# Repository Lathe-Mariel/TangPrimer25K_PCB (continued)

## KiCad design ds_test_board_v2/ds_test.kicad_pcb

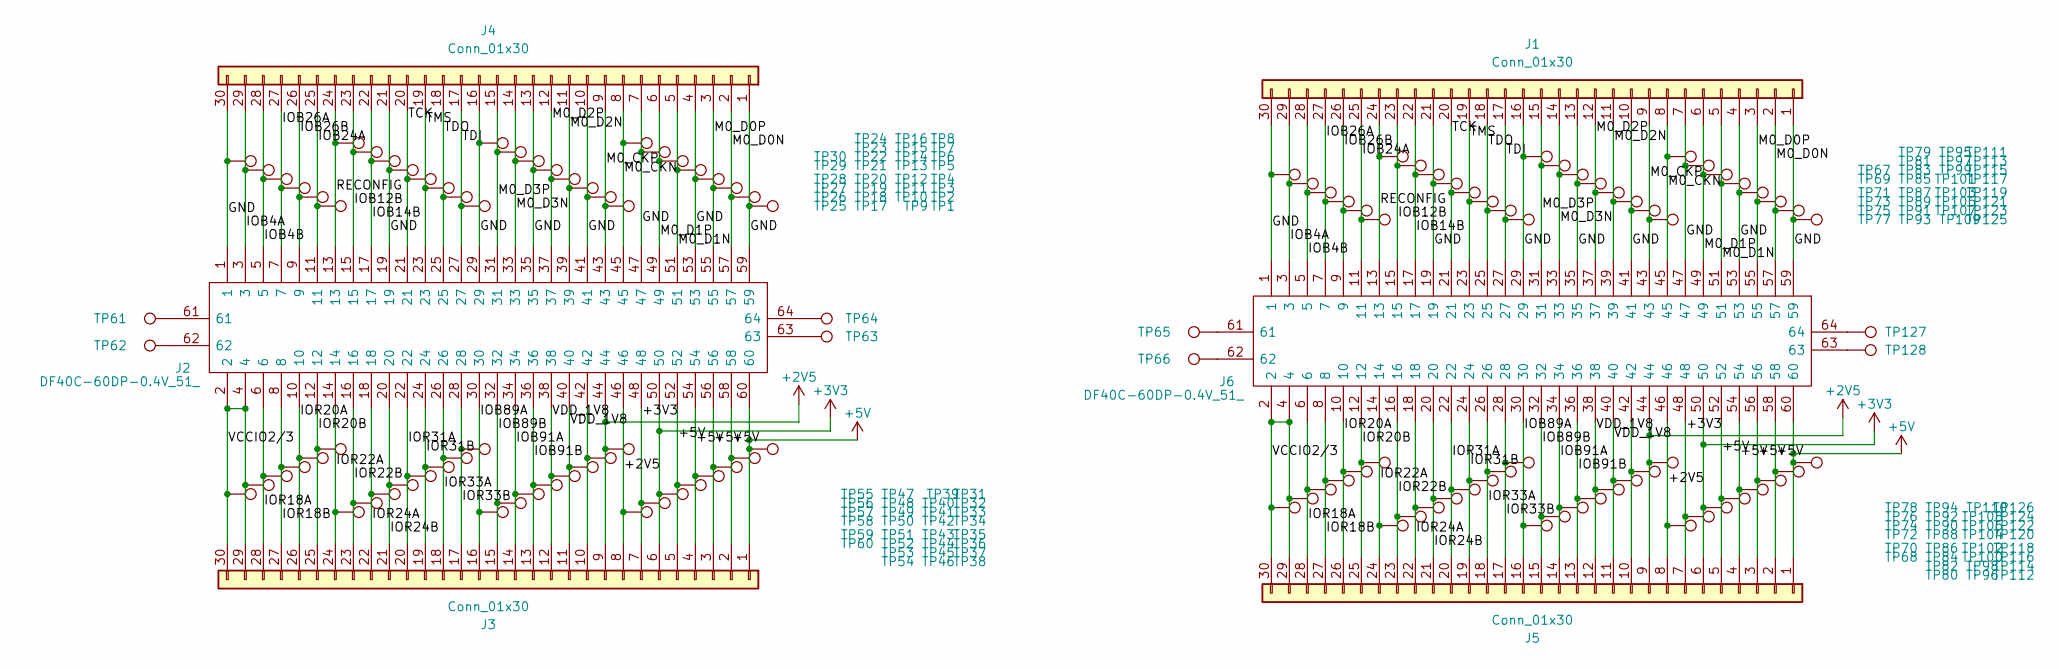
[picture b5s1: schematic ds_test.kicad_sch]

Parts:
J1, J3, J4, J5: Conn_01x30; PinHeader_1x30_P2.54mm_Vertical_SMD_Pin1Left
J2, J6: DF40C-60DP-0.4V_51_; Manufacturer_Part_Number DF40C-60DP-0.4V(51)
TP1, TP2, TP3, TP4, TP5, TP6, TP7, TP8, TP9, TP10, TP11, TP12, TP13, TP14, TP15, TP16, TP17, TP18, TP19, TP20, TP21, TP22, TP23, TP24, TP25, TP26, TP27, TP28, TP29, TP30, TP31, TP32, TP33, TP34, TP35, TP36, TP37, TP38, TP39, TP40, TP41, TP42, TP43, TP44, TP45, TP46, TP47, TP48, TP49, TP50, TP51, TP52, TP53, TP54, TP55, TP56, TP57, TP58, TP59, TP60, TP61, TP62, TP63, TP64, TP65, TP66, TP67, TP68, TP69, TP70, TP71, TP72, TP73, TP74, TP75, TP76, TP77, TP78, TP79, TP80, TP81, TP82, TP83, TP84, TP85, TP86, TP87, TP88, TP89, TP90, TP91, TP92, TP93, TP94, TP95, TP96, TP97, TP98, TP99, TP100, TP101, TP102, TP103, TP104, TP105, TP106, TP107, TP108, TP109, TP110, TP111, TP112, TP113, TP114, TP115, TP116, TP117, TP118, TP119, TP120, TP121, TP122, TP123, TP124, TP125, TP126, TP127, TP128: TestPoint; TestPoint_Pad_1.5x1.5mm

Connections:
+2V5: J2.44, J2.46, J3.8, J3.9, J5.8, J5.9, J6.44, J6.46, TP38.1, TP39.1, TP110.1, TP112.1
+3V3: J2.48, J2.50, J3.6, J3.7, J5.6, J5.7, J6.48, J6.50, TP36.1, TP37.1, TP114.1, TP116.1
+5V: J2.52, J2.54, J2.56, J2.58, J2.60, J3.1, J3.2, J3.3, J3.4, J3.5, J5.1, J5.2, J5.3, J5.4, J5.5, J6.52, J6.54, J6.56, J6.58, J6.60, TP31.1, TP32.1, TP33.1, TP34.1, TP35.1, TP118.1, TP120.1, TP122.1, TP124.1, TP126.1
/GND: J1.1, J1.4, J1.7, J1.10, J1.13, J1.16, J1.21, J1.30, J2.1, J2.19, J2.29, J2.35, J2.41, J2.47, J2.53, J2.59, J4.1, J4.4, J4.7, J4.10, J4.13, J4.16, J4.21, J4.30, J6.1, J6.19, J6.29, J6.35, J6.41, J6.47, J6.53, J6.59, TP1.1, TP4.1, TP7.1, TP10.1, TP13.1, TP16.1, TP21.1, TP30.1, TP67.1, TP85.1, TP95.1, TP101.1, TP107.1, TP113.1, TP119.1, TP125.1
/IOB4A: J1.29, J2.3, J4.29, J6.3, TP29.1, TP69.1
/IOB4B: J1.28, J2.5, J4.28, J6.5, TP28.1, TP71.1
/IOB12B: J1.23, J2.15, J4.23, J6.15, TP23.1, TP81.1
/IOB14B: J1.22, J2.17, J4.22, J6.17, TP22.1, TP83.1
/IOB24A: J1.25, J2.11, J4.25, J6.11, TP25.1, TP77.1
/IOB26A: J1.27, J2.7, J4.27, J6.7, TP27.1, TP73.1
/IOB26B: J1.26, J2.9, J4.26, J6.9, TP26.1, TP75.1
/IOB89A: J2.30, J3.16, J5.16, J6.30, TP46.1, TP96.1
/IOB89B: J2.32, J3.15, J5.15, J6.32, TP45.1, TP98.1
/IOB91A: J2.34, J3.14, J5.14, J6.34, TP44.1, TP100.1
/IOB91B: J2.36, J3.13, J5.13, J6.36, TP43.1, TP102.1
/IOR18A: J2.6, J3.28, J5.28, J6.6, TP58.1, TP72.1
/IOR18B: J2.8, J3.27, J5.27, J6.8, TP57.1, TP74.1
/IOR20A: J2.10, J3.26, J5.26, J6.10, TP56.1, TP76.1
/IOR20B: J2.12, J3.25, J5.25, J6.12, TP55.1, TP78.1
/IOR22A: J2.14, J3.24, J5.24, J6.14, TP54.1, TP80.1
/IOR22B: J2.16, J3.23, J5.23, J6.16, TP53.1, TP82.1
/IOR24A: J2.18, J3.22, J5.22, J6.18, TP52.1, TP84.1
/IOR24B: J2.20, J3.21, J5.21, J6.20, TP51.1, TP86.1
/IOR31A: J2.22, J3.20, J5.20, J6.22, TP50.1, TP88.1
/IOR31B: J2.24, J3.19, J5.19, J6.24, TP49.1, TP90.1
/IOR33A: J2.26, J3.18, J5.18, J6.26, TP48.1, TP92.1
/IOR33B: J2.28, J3.17, J5.17, J6.28, TP47.1, TP94.1
/M0_CKN: J1.8, J2.45, J4.8, J6.45, TP8.1, TP111.1
/M0_CKP: J1.9, J2.43, J4.9, J6.43, TP9.1, TP109.1
/M0_D0N: J1.2, J2.57, J4.2, J6.57, TP2.1, TP123.1
/M0_D0P: J1.3, J2.55, J4.3, J6.55, TP3.1, TP121.1
/M0_D1N: J1.5, J2.51, J4.5, J6.51, TP5.1, TP117.1
/M0_D1P: J1.6, J2.49, J4.6, J6.49, TP6.1, TP115.1
/M0_D2N: J1.11, J2.39, J4.11, J6.39, TP11.1, TP105.1
/M0_D2P: J1.12, J2.37, J4.12, J6.37, TP12.1, TP103.1
/M0_D3N: J1.14, J2.33, J4.14, J6.33, TP14.1, TP99.1
/M0_D3P: J1.15, J2.31, J4.15, J6.31, TP15.1, TP97.1
/RECONFIG: J1.24, J2.13, J4.24, J6.13, TP24.1, TP79.1
/TCK: J1.20, J2.21, J4.20, J6.21, TP20.1, TP87.1
/TDI: J1.17, J2.27, J4.17, J6.27, TP17.1, TP93.1
/TDO: J1.18, J2.25, J4.18, J6.25, TP18.1, TP91.1
/TMS: J1.19, J2.23, J4.19, J6.23, TP19.1, TP89.1
/VCCIO2/3: J2.2, J2.4, J3.29, J3.30, J5.29, J5.30, J6.2, J6.4, TP59.1, TP60.1, TP68.1, TP70.1
/VDD_1V8: J2.38, J2.40, J3.11, J3.12, J5.11, J5.12, J6.38, J6.40, TP41.1, TP42.1, TP104.1, TP106.1
unnamed: J2.61, TP61.1
unnamed: J2.62, TP62.1
unnamed: J2.63, TP63.1
unnamed: J2.64, TP64.1
unnamed: J2.42, J3.10, TP40.1
unnamed: J5.10, J6.42, TP108.1
unnamed: J6.61, TP65.1
unnamed: J6.62, TP66.1
unnamed: J6.63, TP128.1
unnamed: J6.64, TP127.1

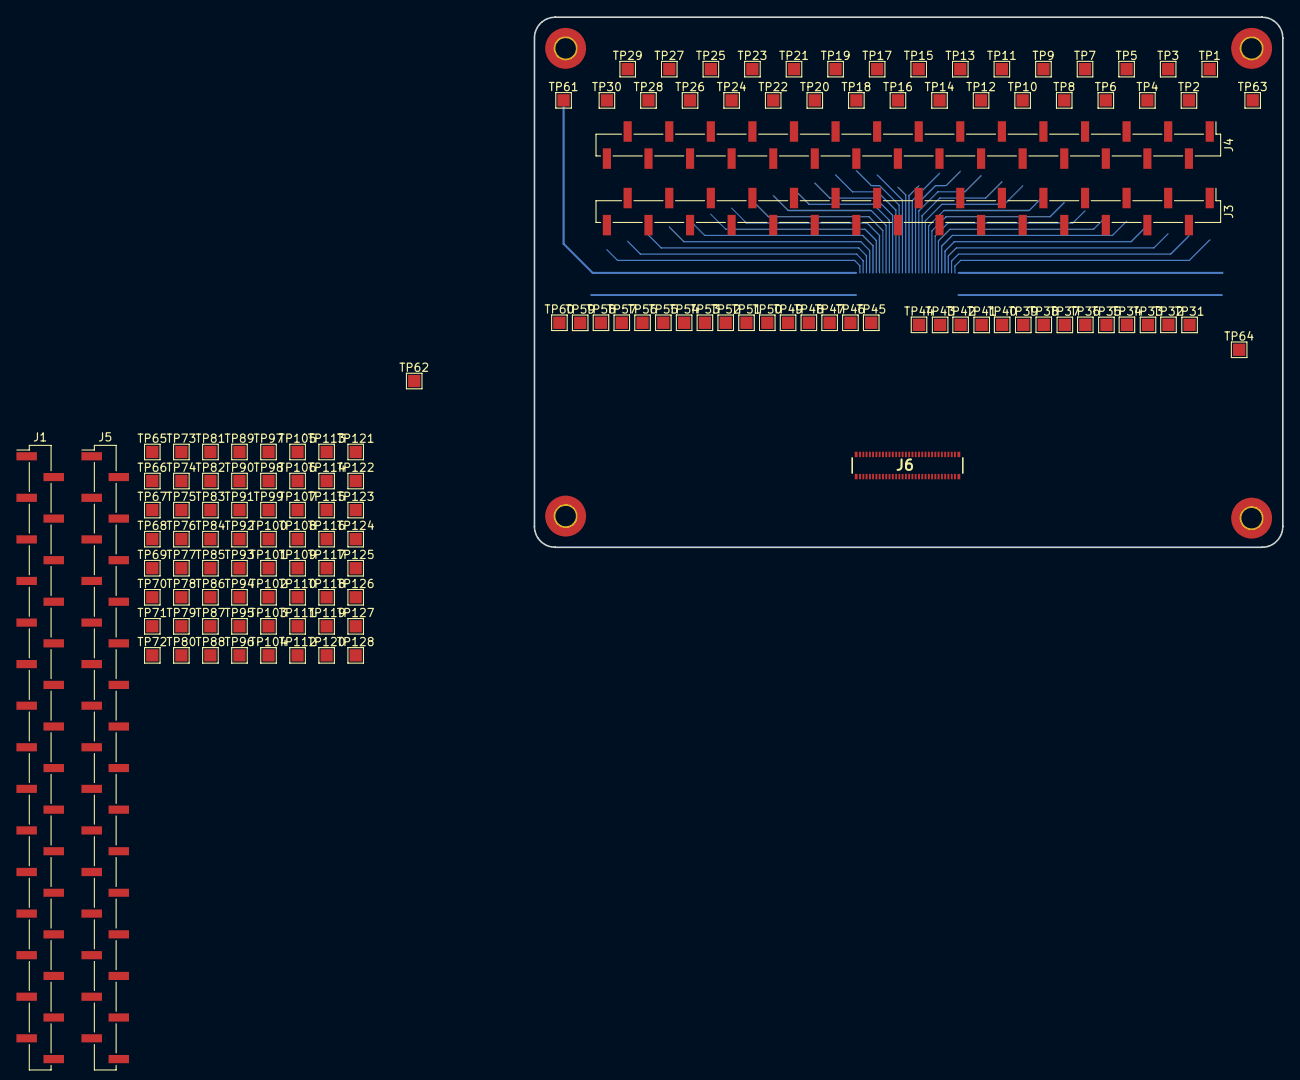
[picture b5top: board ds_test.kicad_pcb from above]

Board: 2 copper layers, 91.4 x 64.8 mm, 134 parts (1 on the bottom side), 54 nets.

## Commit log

2023-11-30 1130
2023-11-30 1201
2023-12-04 1204
2023-12-04 1205
2023-12-05 1206
2023-12-10 1211
2023-12-15 1215
2023-12-15 1216
2023-12-18 1218
2023-12-18 1219
2023-12-19 1220
2023-12-22 1222
2024-03-15 0315
2024-03-24 0325
2024-04-09 0409
2024-09-25 0925
